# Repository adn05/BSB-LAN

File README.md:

# BSB-LPB-PPS-LAN

> **About this fork (branch content added on top of upstream BSB-LAN).**
> This repository adapts BSB-LAN to one **Atlantic Alféa Extensa Duo A.I.** heat pump (Siemens **RVS21**, family 211,
> variant 127, BSB bus on X86), running on an **ESP32-C3 SuperMini** plugged into a custom isolated interface board,
> and integrated into **Home Assistant** over MQTT. It is a personal project, not an official BSB-LAN release:
> for any other installation, use the [upstream project](https://github.com/fredlcore/BSB-LAN).
>
> Additions (the upstream code in `BSB_LAN/` only gets a few compile-time guards):
> - `alfea/config/`, `alfea/params/`: configuration, full 211/127 parameter list, Home Assistant selection, write whitelist;
> - `alfea/homeassistant/`: thermostat package (room setpoint overrides, DHW boost) and dashboard;
> - `alfea/hardware/`: interface board (KiCad 9) and 3D-printable enclosure;
> - `alfea/tools/`, `docker/`: build in Docker (`sh docker/compiler.sh`), flashing and USB console (`alfea/tools/flasher.py`);
> - documentation, in French: [`docs/claude/README.md`](docs/claude/README.md).

Die deutsche Fassung dieser Datei gibt es [hier](README_de.md).

Before getting started, please read through the manual [here](https://docs.bsb-lan.de).

BSB-LAN is a software/hardware solution for accessing the “Boiler-System-Bus” (BSB), the “Local-Process-Bus (LPB)” and the “Punkt-zu-Punkt-Schnittstelle” (PPS). The adapter is available for various *ESP32*-based microcontrollers (ESP32 NodeMCU, Olimex EVB, Olimex POE-ISO) as well as for an *Arduino Due* with Ethernet shield. It allows accessing the heating systems from Atlantic, Brötje, Elco and many other manufacturers via LAN/WLAN, provided that they use one of the Siemens controllers listed below. BSB-LAN makes it possible to control or regulate the heating and log any given values. This project supports almost all parameters available on the heating systems and can be used for in a comprehensive home automation environment.  

---

***Interface kits available!***  
**Interface boards are available for the ESP32 upon request. These can simply be plugged on top of one of the listed microcontrollers.Getting the board from here helps supporting this project in the future, so if you are interested, please send Frederik an e-mail (German or English) to <br /> bsb (ät) code-it.de <br /> for further informations.**  

---  

Using the adapter and the BSB-LAN software, various values and parameters can easily be monitored, logged and, if so desired, controlled and changed via a web-interface.
Optional integration into existing smart home systems such as FHEM, openHAB, HomeMatic, ioBroker, Loxone, IP-Symcon, EDOMI, Home Assistant, SmartHomeNG or Node-RED is possible via MQTT, JSON or HTTP access. 
The adapter can also be used as a standalone logger without LAN or Internet connection when using a microSD card (MBR partition / FAT format).  
Temperature and humidity sensors can also be connected and their data can also be logged and analyzed. The option of integrating your own code into the BSB-LAN software also offers a wide range of expansion options. 
        
**In the following, some model series from different manufacturers are listed, which usually have installed BSB-LAN compatible controllers:**  
- Brötje: BBK, BBS, BGB, BLW (**see exceptions below!**), BMK, BMR, BOB, BSK, BSW, Eurocontrol, ISR, LogoBloc, SGB, SOB, SPK, WBC (**see exceptions below!**), WBS (**see exceptions below!**), WGB (**see exceptions below!**), WMC, WMS, WOB
- **Not working Brötje models: BOK, BLW Eco, BLW Eco.2, BLW Mono, BLW Mono.1, BLW Neo, BLW Pro.1, BLW Split, BSW Neo, WBC 22.1/28.1, WBC 14.1/22.1, WGB-K 22.1/28.1, WGB 14.1/22.1/28.1/38.1, WHB, WHC, WHS, WLC, WLS and all others with IWR controller**  
- Bösch: heat pumps with RVS controller type
- Elco: Aerotop (**not EVO LN / Mono / Mono.2 / Split / Split.2!**), Aquatop, Rendamax, Straton, Thision (**not Thision Mini!**), Thision S, Thision S Plus, Trigon S Plus
- Alarko: Aldens WM/WS
- ATAG: QR
- Atlantic: Axeo, Alféa Excellia A.I., Alféa Extensa A.I., Hynea hybrid duo gaz, Navistem, Perfinox, Varmax
- Austria Email: LWP, LWPK
- Baxi: Luna Platinum, Luna Duo, Block Kondens
- Boesch: SLS
- Chappée: Luna, Klista
- CitrinSolar: proClima
- CTA: Optiheat
- CTC: 380 IC
- Deville: 9942, 9981
- District heating: RVD230
- Eco: AiWA, AW, BW, DW, heatLite, Star, TBW, WW, WWi, TWW
- Ecostar: Ecodense WT-S 45
- Etna: II GWS
- EVI Heat: Combi-7
- Ferroli: HMP
- Froeling: Rendagas Plus
- Fujitsu Waterstage: Comfort, Duo, WOHA, WSHA, WSYA, WSYK, WSYP
- Gebwell: T2
- Geminox: Thrs
- General: (aka Fujitsu Waterstage) WC13F / WOC13RIYF / WGHA 100DG
- Gorenje: Aerogor Compact, Aerogor Compact EVI, Aerogor ECO Inverter 10 A, Aerogor Split AW, Aerogor Split HD, Aerogor Split HD EVI, Aquagor, Aquagor EVI, Geogor All-In-One, Terragor, Terragor EVI
- Grünenwald: Greenheat
- GS: UnoTec
- Hansa: SND
- Herz: Commotherm 5 DeLuxe
- Hotjet: One2, Wx, ZETXe, ZETXi
- Ideal Heating: Halo Air, Logic Air Heat Pump
- Interdomo: Domostar GBK 25H/SH, OBK (HC 232)
- MAN/MHG: Ecostar 200
- MHG: ecoWP Xe, Procon E
- Oilon: CUBE House, GT, SH, SHx
- Olymp: RegelStar 3000, SHS, WHS
- Palazzetti: Choro Sistema Calore
- Potterton: Paramount
- Robur: Comfort Controller, K18 Simplygas / Hybrigas
- Sieger: TG11
- Šildymo Technologijų Centras (ŠTC): STC9
- Sixmadun: TG11BE
- Smartheat: UI400
- SSP: Proburner
- Strebel: S-ASX
- Sunex: Nexus
- Termomax: Termo ÖV
- Thercon: Therma Silent Coax Single, THERMA Silent Coax Combi 300/500
- Thermics: Energie
- Thermital: TBox Clima TOP
- Tifell: Biofell
- Variheat: 110C
- Viadrus : Claudius K1, K2
- Viessmann: Vitotwin 300-W (exclusively!)
- Wamak: AiWa, DB
- Weishaupt: WTU  

If your heater has one of the following controllers, but your model ist not listed in our manual, feel free to get in touch with us, as these models have been confirmed working:  
AVS37, AVS55, AVS71, AVS74, AVS75, AVS77, AVS79, LMS14, LMS15, LMS15, LMU64, LMU74, LMU75, RVA61, RVA63, RVA33, RVA36, RVA43, RVA46, RVA47, RVA53, RVA60, RVA61, RVA63, RVA65, RVA66, RVC32, RVD110, RVD115, RVD120, RVD125, RVD130, RVD135, RVD139, RVD140, RVD144, RVD145, RVD230, RVD235, RVD240, RVD245, RVD250, RVD255, RVD260, RVD265, RVL469, RVL470, RVL471, RVL472, RVL479, RVL480, RVL481, RVL482, RVP320, RVP330, RVP340, RVP350, RVP351, RVP360, RVP361, RVP5xx, RVS13, RVS21, RVS23, RVS26, RVS41, RVS43, RVS46, RVS47, RVS51, RVS53, RVS61, RVS63, RVS65, RVS68, RWI65, WRI80
<BR><BR>

<B>Attention!</B><BR>
Some companies which previously used BSB/LPB in their heating systems have now switched to other systems for their lower-cost devices. Examples are Brötje's WLC/WLS/BOK series. These are not compatible with BSB/LPB and only allow very limited parameters to be configured by the user. If you have one of these heating systems, you are so far out of luck to configure and monitor your heating system as it can be done with the more expensive (but BSB/LPB compatible) devices mentioned above among others.
In addition, there are now also Siemens controllers that no longer expose BSB/LPB connectors, but use different bus systems, for example the LMU34 and the Climatix/POS-series.
<BR><BR>
Instructions on how to configure etc. can be found in the <A HREF="https://docs.bsb-lan.de">manual</A>.<BR>
The forum thread that led to the development of this interface can be found <A HREF="http://forum.fhem.de/index.php?topic=29762.new;topicseen#new">here</A>.<BR>
(Forum is in German, but several members speak English)

Please take note that while the board can also be used on the Raspberry Pi, the software provided here only runs on the ESP32 and Arduino Due respectively! For using the board with the Pi, you have to use the software bsb_gateway which is available <A HREF="https://github.com/loehnertj/bsbgateway">here</A>. Please also note that the functionality differs significantly, and that you would have to contact the author of bsb_gateway for any question related to it.

Web-Interface screenshots:

BSB-Board populated for ESP32 Olimex boards:

BSB-Board on Olimex POE inside the project's 3D-printed case:

<br />This work is licensed under a <a rel="license" href="http://creativecommons.org/licenses/by-nc-sa/4.0/">Creative Commons Attribution-NonCommercial-ShareAlike 4.0 International License</a>.

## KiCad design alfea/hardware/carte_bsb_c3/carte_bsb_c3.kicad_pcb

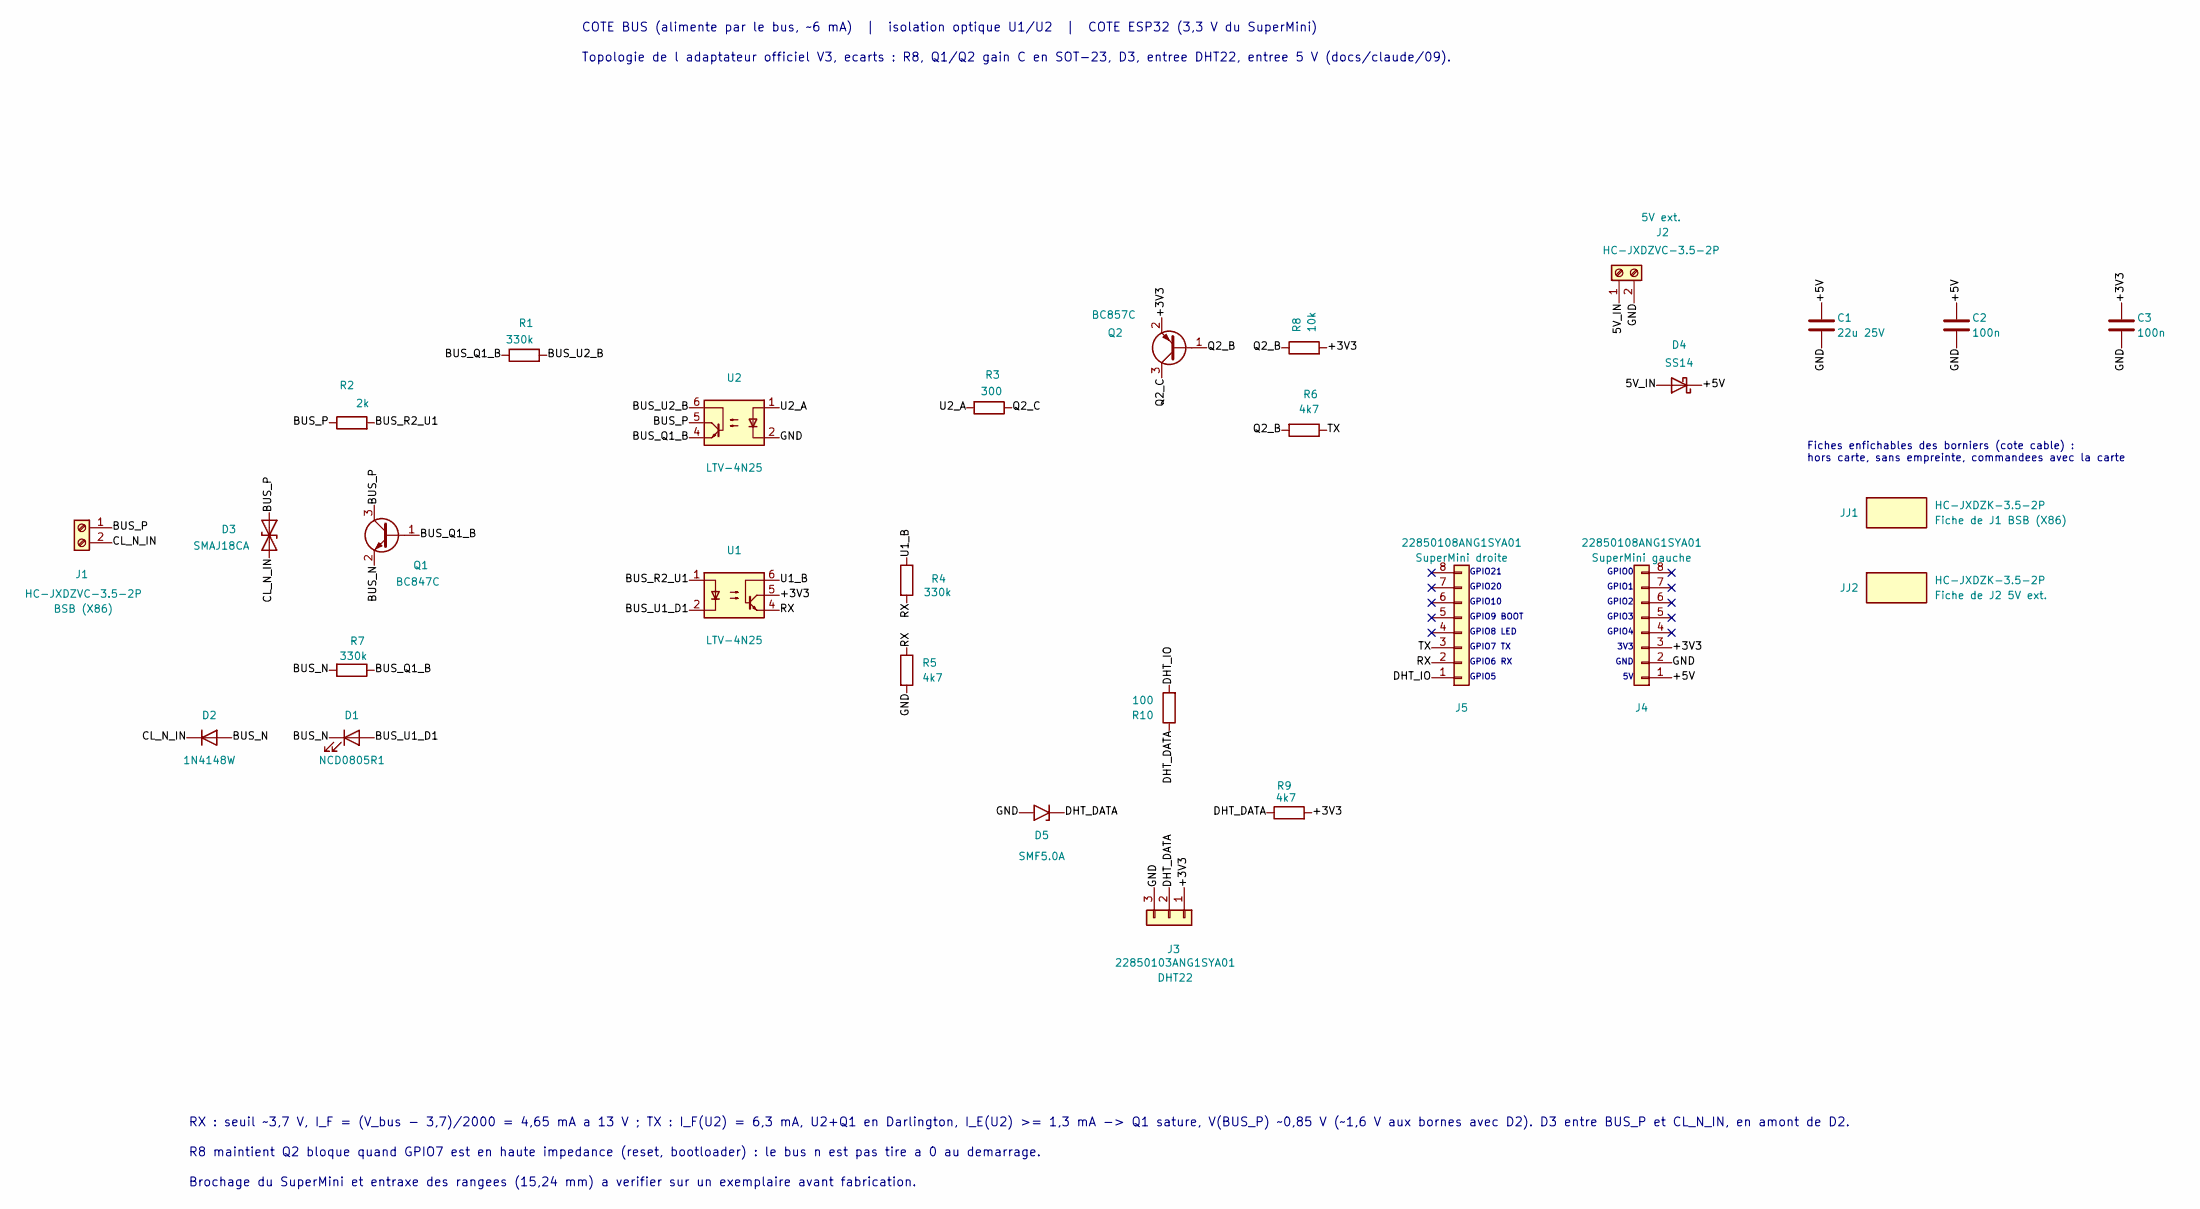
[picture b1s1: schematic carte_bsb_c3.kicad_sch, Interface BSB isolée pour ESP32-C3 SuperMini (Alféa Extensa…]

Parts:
C1: 22u 25V; C_1206_3216Metric; MPN Samsung Electro-Mechanics CL31A226KAHNN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; JLCPCB Part # C12891
C2, C3: 100n; C_0805_2012Metric; MPN YAGEO CC0805KRX7R9BB104; JLCPCB Part # C49678
D1: NCD0805R1; LED_0805_2012Metric; MPN Foshan NationStar Optoelectronics NCD08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; JLCPCB Part # C84256
D2: 1N4148W; D_SOD-123; MPN ST(Semtech) 1N4148W; JLCPCB Part # C81598
D3: SMAJ18CA; D_SMA; MPN hongjiacheng SMAJ18CA; JLCPCB Part # C19077539
D4: SS14; D_SMA; MPN MDD(Microdiode Semiconductor) SS14; JLCPCB Part # C2480
D5: SMF5.0A; D_SOD-123F; MPN hongjiacheng SMF5.0A; JLCPCB Part # C19077497
J1, J2: HC-JXDZVC-3.5-2P; PhoenixContact_MCV_1,5_2-G-3.5_1x02_P3.50mm_Vertical; MPN Hong Cheng HC-JXDZVC-3.5-2P; JLCPCB Part # C51927058
J3: 22850103ANG1SYA01; PinSocket_1x03_P2.54mm_Vertical; MPN JILN 22850103ANG1SYA01; JLCPCB Part # C41431926
J4, J5: 22850108ANG1SYA01; PinSocket_1x08_P2.54mm_Vertical; MPN JILN 22850108ANG1SYA01; JLCPCB Part # C429957
JJ1, JJ2: HC-JXDZK-3.5-2P; MPN Hong Cheng HC-JXDZK-3.5-2P; JLCPCB Part # C51927077
Q1: BC847C; SOT-23; MPN hongjiacheng BC847C; JLCPCB Part # C7420337
Q2: BC857C; SOT-23; MPN hongjiacheng BC857C; JLCPCB Part # C20069137
R1, R4, R7: 330k; R_0805_2012Metric; MPN UNI-ROYAL(Uniroyal Elec) 0805W8F3303T5E; JLCPCB Part # C17629
R2: 2k; R_1206_3216Metric; MPN UNI-ROYAL(Uniroyal Elec) 1206W4F2001T5E; JLCPCB Part # C17944
R3: 300; R_0805_2012Metric; MPN UNI-ROYAL(Uniroyal Elec) 0805W8F3000T5E; JLCPCB Part # C17617
R5, R6, R9: 4k7; R_0805_2012Metric; MPN UNI-ROYAL(Uniroyal Elec) 0805W8F4701T5E; JLCPCB Part # C17673
R8: 10k; R_0805_2012Metric; MPN UNI-ROYAL(Uniroyal Elec) 0805W8F1002T5E; JLCPCB Part # C17414
R10: 100; R_0805_2012Metric; MPN UNI-ROYAL(Uniroyal Elec) 0805W8F1000T5E; JLCPCB Part # C17408
U1, U2: LTV-4N25; DIP-6_W7.62mm; MPN Lite-On LTV-4N25; JLCPCB Part # C118160

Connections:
/5V_IN: D4.2 (A), J2.1
/+3V3: C3.1, J3.1, J4.3, Q2.2 (E), R8.2, R9.2, U1.5
/+5V: C1.1, C2.1, D4.1 (K), J4.1
/BUS_N: D1.1 (K), D2.2 (A), Q1.2 (E), R7.2
/BUS_P: D3.1 (A1), J1.1, Q1.3 (C), R2.1, U2.5
/BUS_Q1_B: Q1.1 (B), R1.1, R7.1, U2.4
/BUS_R2_U1: R2.2, U1.1
/BUS_U1_D1: D1.2 (A), U1.2
/BUS_U2_B: R1.2, U2.6
/CL_N_IN: D2.1 (K), D3.2 (A2), J1.2
/DHT_DATA: D5.1 (A1), J3.2, R9.1, R10.1
/DHT_IO: J5.1, R10.2
/GND: C1.2, C2.2, C3.2, D5.2 (A2), J2.2, J3.3, J4.2, R5.2, U2.2
/Q2_B: Q2.1 (B), R6.2, R8.1
/Q2_C: Q2.3 (C), R3.1
/RX: J5.2, R4.2, R5.1, U1.4
/TX: J5.3, R6.1
/U1_B: R4.1, U1.6
/U2_A: R3.2, U2.1

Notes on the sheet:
GPIO6 RX
RX : seuil ~3,7 V, I_F = (V_bus - 3,7)/2000 = 4,65 mA a 13 V ; TX : I_F(U2) = 6,3 mA, U2+Q1 en Darlington, I_E(U2) >= 1,3 mA -> Q1 sature, V(BUS_P) ~0,85 V (~1,6 V aux bornes avec D2). D3 entre BUS_P et CL_N_IN, en amont de D2.
GPIO1
Brochage du SuperMini et entraxe des rangees (15,24 mm) a verifier sur un exemplaire avant fabrication.
GPIO7 TX
GPIO3
GPIO20
GPIO9 BOOT
GPIO5
GPIO0
R8 maintient Q2 bloque quand GPIO7 est en haute impedance (reset, bootloader) : le bus n est pas tire a 0 au demarrage.
Topologie de l adaptateur officiel V3, ecarts : R8, Q1/Q2 gain C en SOT-23, D3, entree DHT22, entree 5 V (docs/claude/09).
3V3
GND
GPIO21
GPIO4
GPIO2
GPIO8 LED
GPIO10
COTE BUS (alimente par le bus, ~6 mA) | isolation optique U1/U2 | COTE ESP32 (3,3 V du SuperMini)
Fiches enfichables des borniers (cote cable) : hors carte, sans empreinte, commandees avec la carte

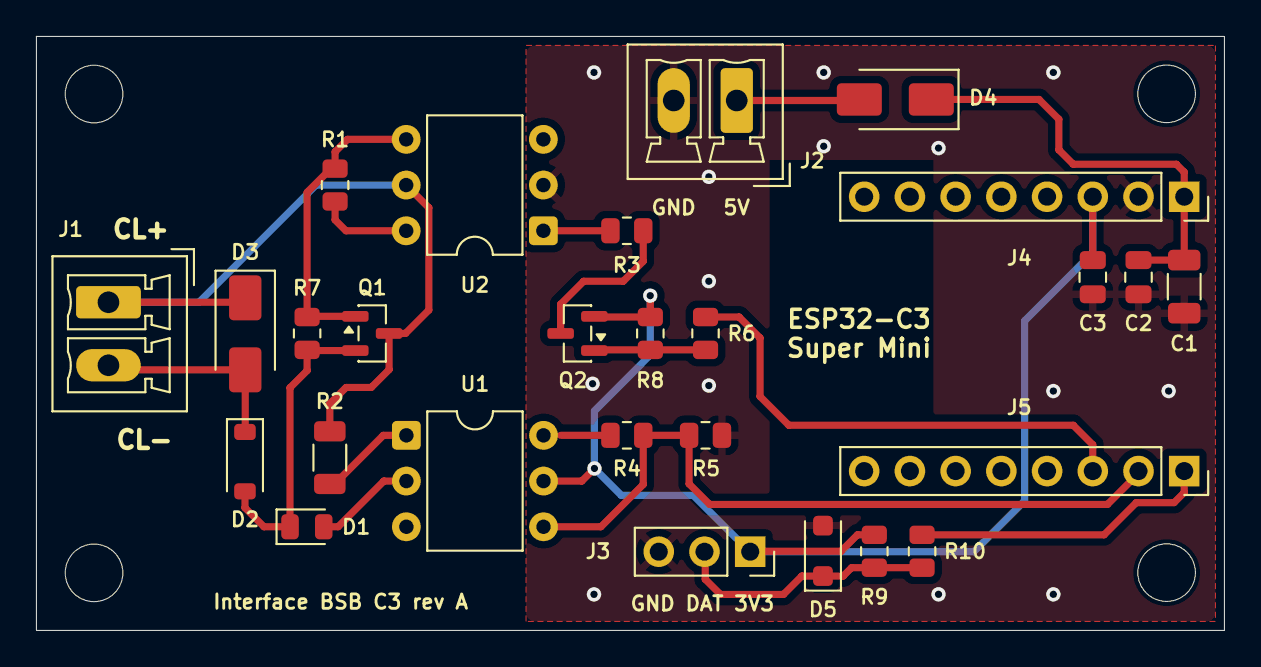
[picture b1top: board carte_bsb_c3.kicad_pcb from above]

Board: 2 copper layers, 66.0 x 33.0 mm, 31 parts (0 on the bottom side), 19 nets.

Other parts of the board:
H1, H2, H3, H4: MountingHole_3.2mm_M3

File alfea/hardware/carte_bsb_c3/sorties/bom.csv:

"Designator","Comment","Footprint","Quantity","JLCPCB Part #","Product link","MPN"
"C1","22u 25V","Capacitor_SMD:C_1206_3216Metric","1","C12891","https://jlcpcb.com/partdetail/13537-CL31A226KAHNNNE/C12891","Samsung Electro-Mechanics CL31A226KAHNNNE"
"C2,C3","100n","Capacitor_SMD:C_0805_2012Metric","2","C49678","https://jlcpcb.com/partdetail/YAGEO-CC0805KRX7R9BB104/C49678","YAGEO CC0805KRX7R9BB104"
"D1","NCD0805R1","LED_SMD:LED_0805_2012Metric","1","C84256","https://jlcpcb.com/partdetail/85425-NCD0805R1/C84256","Foshan NationStar Optoelectronics NCD0805R1"
"D2","1N4148W","Diode_SMD:D_SOD-123","1","C81598","https://jlcpcb.com/partdetail/ST_Semtech-1N4148W/C81598","ST(Semtech) 1N4148W"
"D3","SMAJ18CA","Diode_SMD:D_SMA","1","C19077539","https://jlcpcb.com/partdetail/hongjiacheng-SMAJ18CA/C19077539","hongjiacheng SMAJ18CA"
"D4","SS14","Diode_SMD:D_SMA","1","C2480","https://jlcpcb.com/partdetail/MDD_Microdiode_Semiconductor-S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","MDD(Microdiode Semiconductor) SS14"
"D5","SMF5.0A","Diode_SMD:D_SOD-123F","1","C19077497","https://jlcpcb.com/partdetail/hongjiacheng-SMF50A/C19077497","hongjiacheng SMF5.0A"
"J1,J2","HC-JXDZVC-3.5-2P","Connector_Phoenix_MC:PhoenixContact_MCV_1,5_2-G-3.5_1x02_P3.50mm_Vertical","2","C51927058","https://jlcpcb.com/partdetail/HongCheng-HC_JXDZVC_3_52P/C51927058","Hong Cheng HC-JXDZVC-3.5-2P"
"J3","22850103ANG1SYA01","Connector_PinSocket_2.54mm:PinSocket_1x03_P2.54mm_Vertical","1","C41431926","https://jlcpcb.com/partdetail/JILN-22850103ANG1SYA01/C41431926","JILN 22850103ANG1SYA01"
"J4,J5","22850108ANG1SYA01","Connector_PinSocket_2.54mm:PinSocket_1x08_P2.54mm_Vertical","2","C429957","https://jlcpcb.com/partdetail/JILN-22850108ANG1SYA01/C429957","JILN 22850108ANG1SYA01"
"JJ1,JJ2","HC-JXDZK-3.5-2P","","2","C51927077","https://jlcpcb.com/partdetail/HongCheng-HC_JXDZK_3_52P/C51927077","Hong Cheng HC-JXDZK-3.5-2P"
"Q1","BC847C","Package_TO_SOT_SMD:SOT-23","1","C7420337","https://jlcpcb.com/partdetail/hongjiacheng-BC847C/C7420337","hongjiacheng BC847C"
"Q2","BC857C","Package_TO_SOT_SMD:SOT-23","1","C20069137","https://jlcpcb.com/partdetail/hongjiacheng-BC857C/C20069137","hongjiacheng BC857C"
"R1,R4,R7","330k","Resistor_SMD:R_0805_2012Metric","3","C17629","https://jlcpcb.com/partdetail/18317-0805W8F3303T5E/C17629","UNI-ROYAL(Uniroyal Elec) 0805W8F3303T5E"
"R2","2k","Resistor_SMD:R_1206_3216Metric","1","C17944","https://jlcpcb.com/partdetail/18632-1206W4F2001T5E/C17944","UNI-ROYAL(Uniroyal Elec) 1206W4F2001T5E"
"R3","300","Resistor_SMD:R_0805_2012Metric","1","C17617","https://jlcpcb.com/partdetail/18305-0805W8F3000T5E/C17617","UNI-ROYAL(Uniroyal Elec) 0805W8F3000T5E"
"R5,R6,R9","4k7","Resistor_SMD:R_0805_2012Metric","3","C17673","https://jlcpcb.com/partdetail/18361-0805W8F4701T5E/C17673","UNI-ROYAL(Uniroyal Elec) 0805W8F4701T5E"
"R8","10k","Resistor_SMD:R_0805_2012Metric","1","C17414","https://jlcpcb.com/partdetail/18102-0805W8F1002T5E/C17414","UNI-ROYAL(Uniroyal Elec) 0805W8F1002T5E"
"R10","100","Resistor_SMD:R_0805_2012Metric","1","C17408","https://jlcpcb.com/partdetail/18096-0805W8F1000T5E/C17408","UNI-ROYAL(Uniroyal Elec) 0805W8F1000T5E"
"U1,U2","LTV-4N25","Package_DIP:DIP-6_W7.62mm","2","C118160","https://jlcpcb.com/partdetail/LiteOn-LTV4N25/C118160","Lite-On LTV-4N25"

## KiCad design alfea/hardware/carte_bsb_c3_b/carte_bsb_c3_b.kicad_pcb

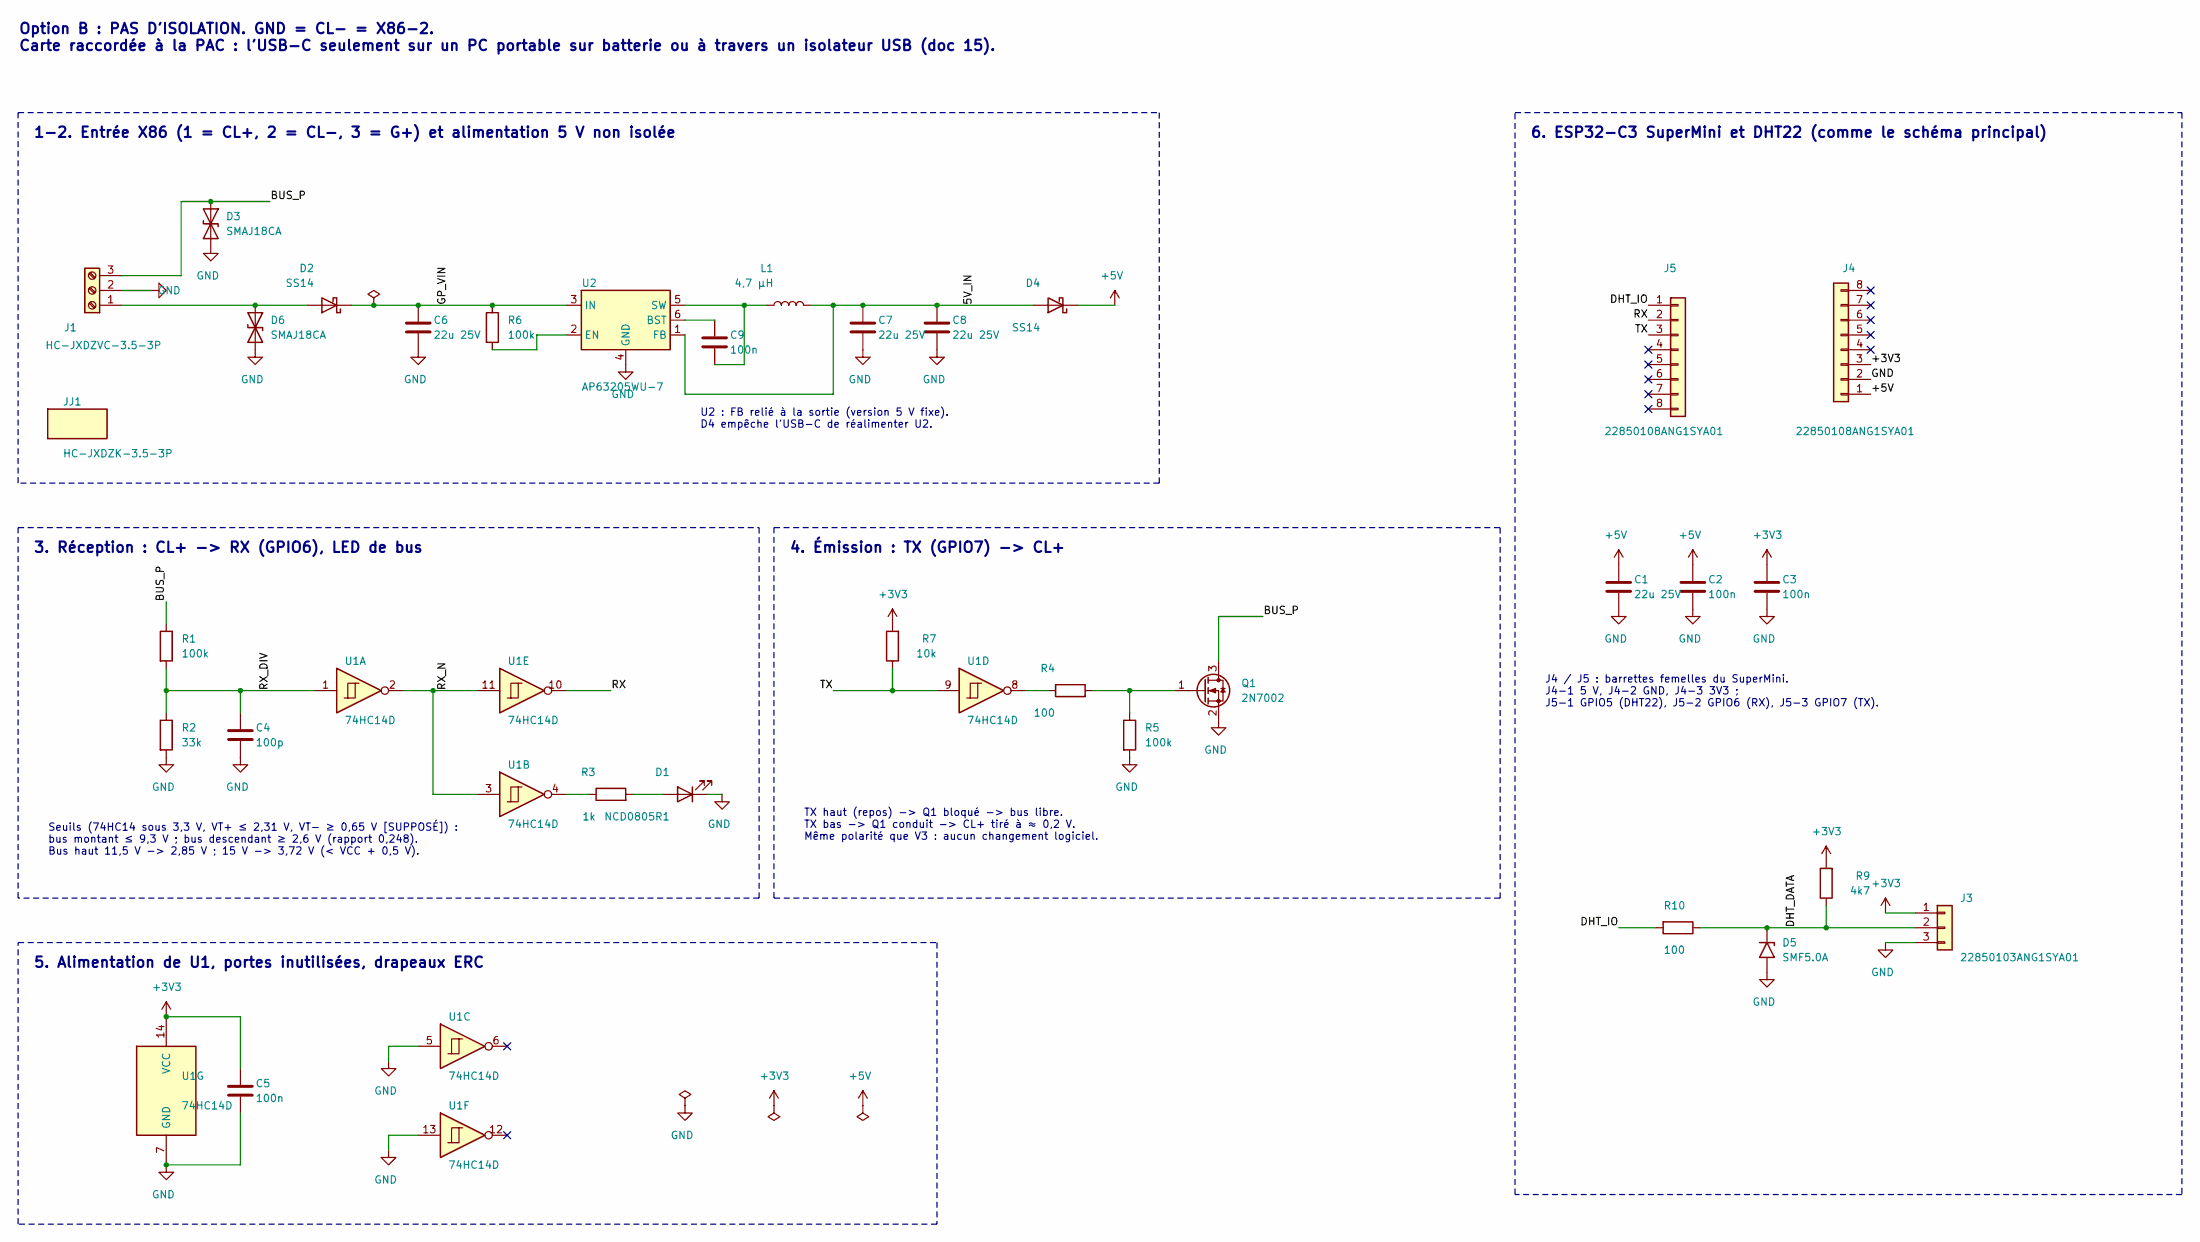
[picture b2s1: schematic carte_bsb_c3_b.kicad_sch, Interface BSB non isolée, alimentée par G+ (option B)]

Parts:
C1, C6, C7, C8: 22u 25V; C_1206_3216Metric; MPN Samsung Electro-Mechanics CL31A226KAHNN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; JLCPCB Part # C12891
C2, C3, C5, C9: 100n; C_0805_2012Metric; MPN YAGEO CC0805KRX7R9BB104; JLCPCB Part # C49678
C4: 100p; C_0805_2012Metric; MPN Samsung Electro-Mechanics CL21C101JBANN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; JLCPCB Part # C1790
D1: NCD0805R1; LED_0805_2012Metric; MPN Foshan NationStar Optoelectronics NCD08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; JLCPCB Part # C84256
D2, D4: SS14; D_SMA; MPN MDD(Microdiode Semiconductor) SS14; JLCPCB Part # C2480
D3, D6: SMAJ18CA; D_SMA; MPN hongjiacheng SMAJ18CA; JLCPCB Part # C19077539
D5: SMF5.0A; D_SOD-123F; MPN hongjiacheng SMF5.0A; JLCPCB Part # C19077497
J1: HC-JXDZVC-3.5-3P; PhoenixContact_MCV_1,5_3-G-3.5_1x03_P3.50mm_Vertical; MPN Hong Cheng HC-JXDZVC-3.5-3P; JLCPCB Part # C51927059
J3: 22850103ANG1SYA01; PinSocket_1x03_P2.54mm_Vertical; MPN JILN 22850103ANG1SYA01; JLCPCB Part # C41431926
J4, J5: 22850108ANG1SYA01; PinSocket_1x08_P2.54mm_Vertical; MPN JILN 22850108ANG1SYA01; JLCPCB Part # C429957
JJ1: HC-JXDZK-3.5-3P; MPN Hong Cheng HC-JXDZK-3.5-3P; JLCPCB Part # C51927078
L1: 4,7 µH; L_Sunlord_SWPA4030S; MPN Sunlord SWPA4030S4R7MT; JLCPCB Part # C57269
Q1: 2N7002; SOT-23; MPN Jiangsu Changjing 2N7002; JLCPCB Part # C8545
R1, R5, R6: 100k; R_0805_2012Metric; MPN UNI-ROYAL(Uniroyal Elec) 0805W8F1003T5E; JLCPCB Part # C149504
R2: 33k; R_0805_2012Metric; MPN UNI-ROYAL(Uniroyal Elec) 0805W8F3302T5E; JLCPCB Part # C17633
R3: 1k; R_0805_2012Metric; MPN UNI-ROYAL(Uniroyal Elec) 0805W8F1001T5E; JLCPCB Part # C17513
R4, R10: 100; R_0805_2012Metric; MPN UNI-ROYAL(Uniroyal Elec) 0805W8F1000T5E; JLCPCB Part # C17408
R7: 10k; R_0805_2012Metric; MPN UNI-ROYAL(Uniroyal Elec) 0805W8F1002T5E; JLCPCB Part # C17414
R9: 4k7; R_0805_2012Metric; MPN UNI-ROYAL(Uniroyal Elec) 0805W8F4701T5E; JLCPCB Part # C17673
U1: 74HC14D; SOIC-14_3.9x8.7mm_P1.27mm; MPN Nexperia 74HC14D,653; JLCPCB Part # C5605
U2: AP63205WU-7; TSOT-23-6; MPN Diodes Incorporated AP63205WU-7; JLCPCB Part # C2071056

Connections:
+3V3: C3.1, C5.1, J3.1, J4.3, R7.2, R9.2, U1.14 (VCC)
+5V: C1.1, C2.1, D4.1 (K), J4.1
/5V_IN: C7.1, C8.1, D4.2 (A), L1.2, U2.1 (FB)
/BUS_P: D3.1 (A1), J1.3, Q1.3 (D), R1.1
/DHT_DATA: D5.1 (A1), J3.2, R9.1, R10.1
/DHT_IO: J5.1, R10.2
/GP_VIN: C6.1, D2.1 (K), R6.1, U2.3 (IN)
/RX: J5.2, U1.10
/RX_DIV: C4.1, R1.2, R2.1, U1.1
/RX_N: U1.2, U1.3, U1.11
/TX: J5.3, R7.1, U1.9
GND: C1.2, C2.2, C3.2, C4.2, C5.2, C6.2, C7.2, C8.2, D1.1 (K), D3.2 (A2), D5.2 (A2), D6.2 (A2), J1.2, J3.3, J4.2, Q1.2 (S), R2.2, R5.2, U1.5, U1.7 (GND), U1.13, U2.4 (GND)
unnamed: D1.2 (A), R3.2
unnamed: D2.2 (A), D6.1 (A1), J1.1
unnamed: Q1.1 (G), R4.2, R5.1
unnamed: R3.1, U1.4
unnamed: R4.1, U1.8
unnamed: C9.1, U2.6 (BST)
unnamed: R6.2, U2.2 (EN)
unnamed: C9.2, L1.1, U2.5 (SW)

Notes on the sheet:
Seuils (74HC14 sous 3,3 V, VT+ ≤ 2,31 V, VT- ≥ 0,65 V [SUPPOSÉ]) : bus montant ≤ 9,3 V ; bus descendant ≥ 2,6 V (rapport 0,248). Bus haut 11,5 V -> 2,85 V ; 15 V -> 3,72 V (< VCC + 0,5 V).
5. Alimentation de U1, portes inutilisées, drapeaux ERC
U2 : FB relié à la sortie (version 5 V fixe). D4 empêche l'USB-C de réalimenter U2.
Option B : PAS D'ISOLATION. GND = CL- = X86-2. Carte raccordée à la PAC : l'USB-C seulement sur un PC portable sur batterie ou à travers un isolateur USB (doc 15).
1-2. Entrée X86 (1 = CL+, 2 = CL-, 3 = G+) et alimentation 5 V non isolée
4. Émission : TX (GPIO7) -> CL+
6. ESP32-C3 SuperMini et DHT22 (comme le schéma principal)
3. Réception : CL+ -> RX (GPIO6), LED de bus
J4 / J5 : barrettes femelles du SuperMini. J4-1 5 V, J4-2 GND, J4-3 3V3 ; J5-1 GPIO5 (DHT22), J5-2 GPIO6 (RX), J5-3 GPIO7 (TX).
TX haut (repos) -> Q1 bloqué -> bus libre. TX bas -> Q1 conduit -> CL+ tiré à ≈ 0,2 V. Même polarité que V3 : aucun changement logiciel.

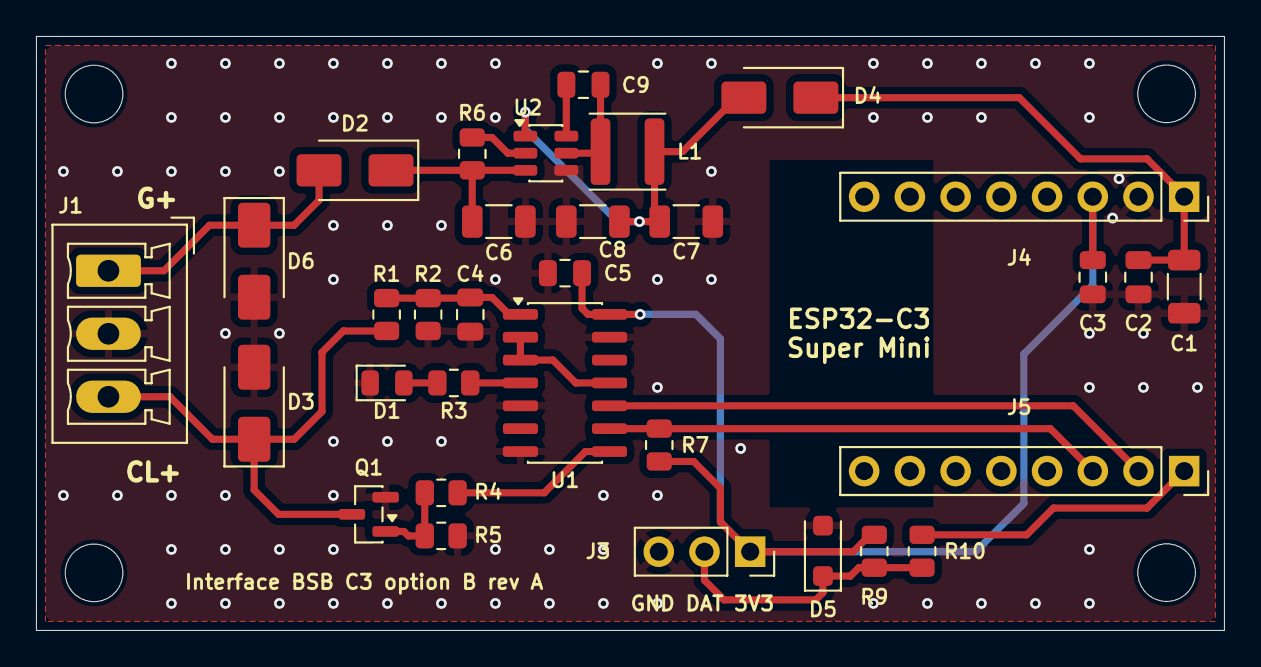
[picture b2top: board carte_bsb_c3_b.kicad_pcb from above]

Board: 2 copper layers, 66.0 x 33.0 mm, 36 parts (0 on the bottom side), 20 nets.

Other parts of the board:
H1, H2, H3, H4: MountingHole_3.2mm_M3

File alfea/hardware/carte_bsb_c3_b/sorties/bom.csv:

"Designator","Comment","Footprint","Quantity","JLCPCB Part #","MPN"
"C1,C6,C7,C8","22u 25V","Capacitor_SMD:C_1206_3216Metric","4","C12891","Samsung Electro-Mechanics CL31A226KAHNNNE"
"C2,C3,C5,C9","100n","Capacitor_SMD:C_0805_2012Metric","4","C49678","YAGEO CC0805KRX7R9BB104"
"C4","100p","Capacitor_SMD:C_0805_2012Metric","1","C1790","Samsung Electro-Mechanics CL21C101JBANNNC"
"D1","NCD0805R1","LED_SMD:LED_0805_2012Metric","1","C84256","Foshan NationStar Optoelectronics NCD0805R1"
"D2,D4","SS14","Diode_SMD:D_SMA","2","C2480","MDD(Microdiode Semiconductor) SS14"
"D3,D6","SMAJ18CA","Diode_SMD:D_SMA","2","C19077539","hongjiacheng SMAJ18CA"
"D5","SMF5.0A","Diode_SMD:D_SOD-123F","1","C19077497","hongjiacheng SMF5.0A"
"J1","HC-JXDZVC-3.5-3P","Connector_Phoenix_MC:PhoenixContact_MCV_1,5_3-G-3.5_1x03_P3.50mm_Vertical","1","C51927059","Hong Cheng HC-JXDZVC-3.5-3P"
"J3","22850103ANG1SYA01","Connector_PinSocket_2.54mm:PinSocket_1x03_P2.54mm_Vertical","1","C41431926","JILN 22850103ANG1SYA01"
"J4,J5","22850108ANG1SYA01","Connector_PinSocket_2.54mm:PinSocket_1x08_P2.54mm_Vertical","2","C429957","JILN 22850108ANG1SYA01"
"JJ1","HC-JXDZK-3.5-3P","","1","C51927078","Hong Cheng HC-JXDZK-3.5-3P"
"L1","4,7 µH","Inductor_SMD:L_Sunlord_SWPA4030S","1","C57269","Sunlord SWPA4030S4R7MT"
"Q1","2N7002","Package_TO_SOT_SMD:SOT-23","1","C8545","Jiangsu Changjing 2N7002"
"R1,R5,R6","100k","Resistor_SMD:R_0805_2012Metric","3","C149504","UNI-ROYAL(Uniroyal Elec) 0805W8F1003T5E"
"R2","33k","Resistor_SMD:R_0805_2012Metric","1","C17633","UNI-ROYAL(Uniroyal Elec) 0805W8F3302T5E"
"R3","1k","Resistor_SMD:R_0805_2012Metric","1","C17513","UNI-ROYAL(Uniroyal Elec) 0805W8F1001T5E"
"R4,R10","100","Resistor_SMD:R_0805_2012Metric","2","C17408","UNI-ROYAL(Uniroyal Elec) 0805W8F1000T5E"
"R7","10k","Resistor_SMD:R_0805_2012Metric","1","C17414","UNI-ROYAL(Uniroyal Elec) 0805W8F1002T5E"
"R9","4k7","Resistor_SMD:R_0805_2012Metric","1","C17673","UNI-ROYAL(Uniroyal Elec) 0805W8F4701T5E"
"U1","74HC14D","Package_SO:SOIC-14_3.9x8.7mm_P1.27mm","1","C5605","Nexperia 74HC14D,653"
"U2","AP63205WU-7","Package_TO_SOT_SMD:TSOT-23-6","1","C2071056","Diodes Incorporated AP63205WU-7"

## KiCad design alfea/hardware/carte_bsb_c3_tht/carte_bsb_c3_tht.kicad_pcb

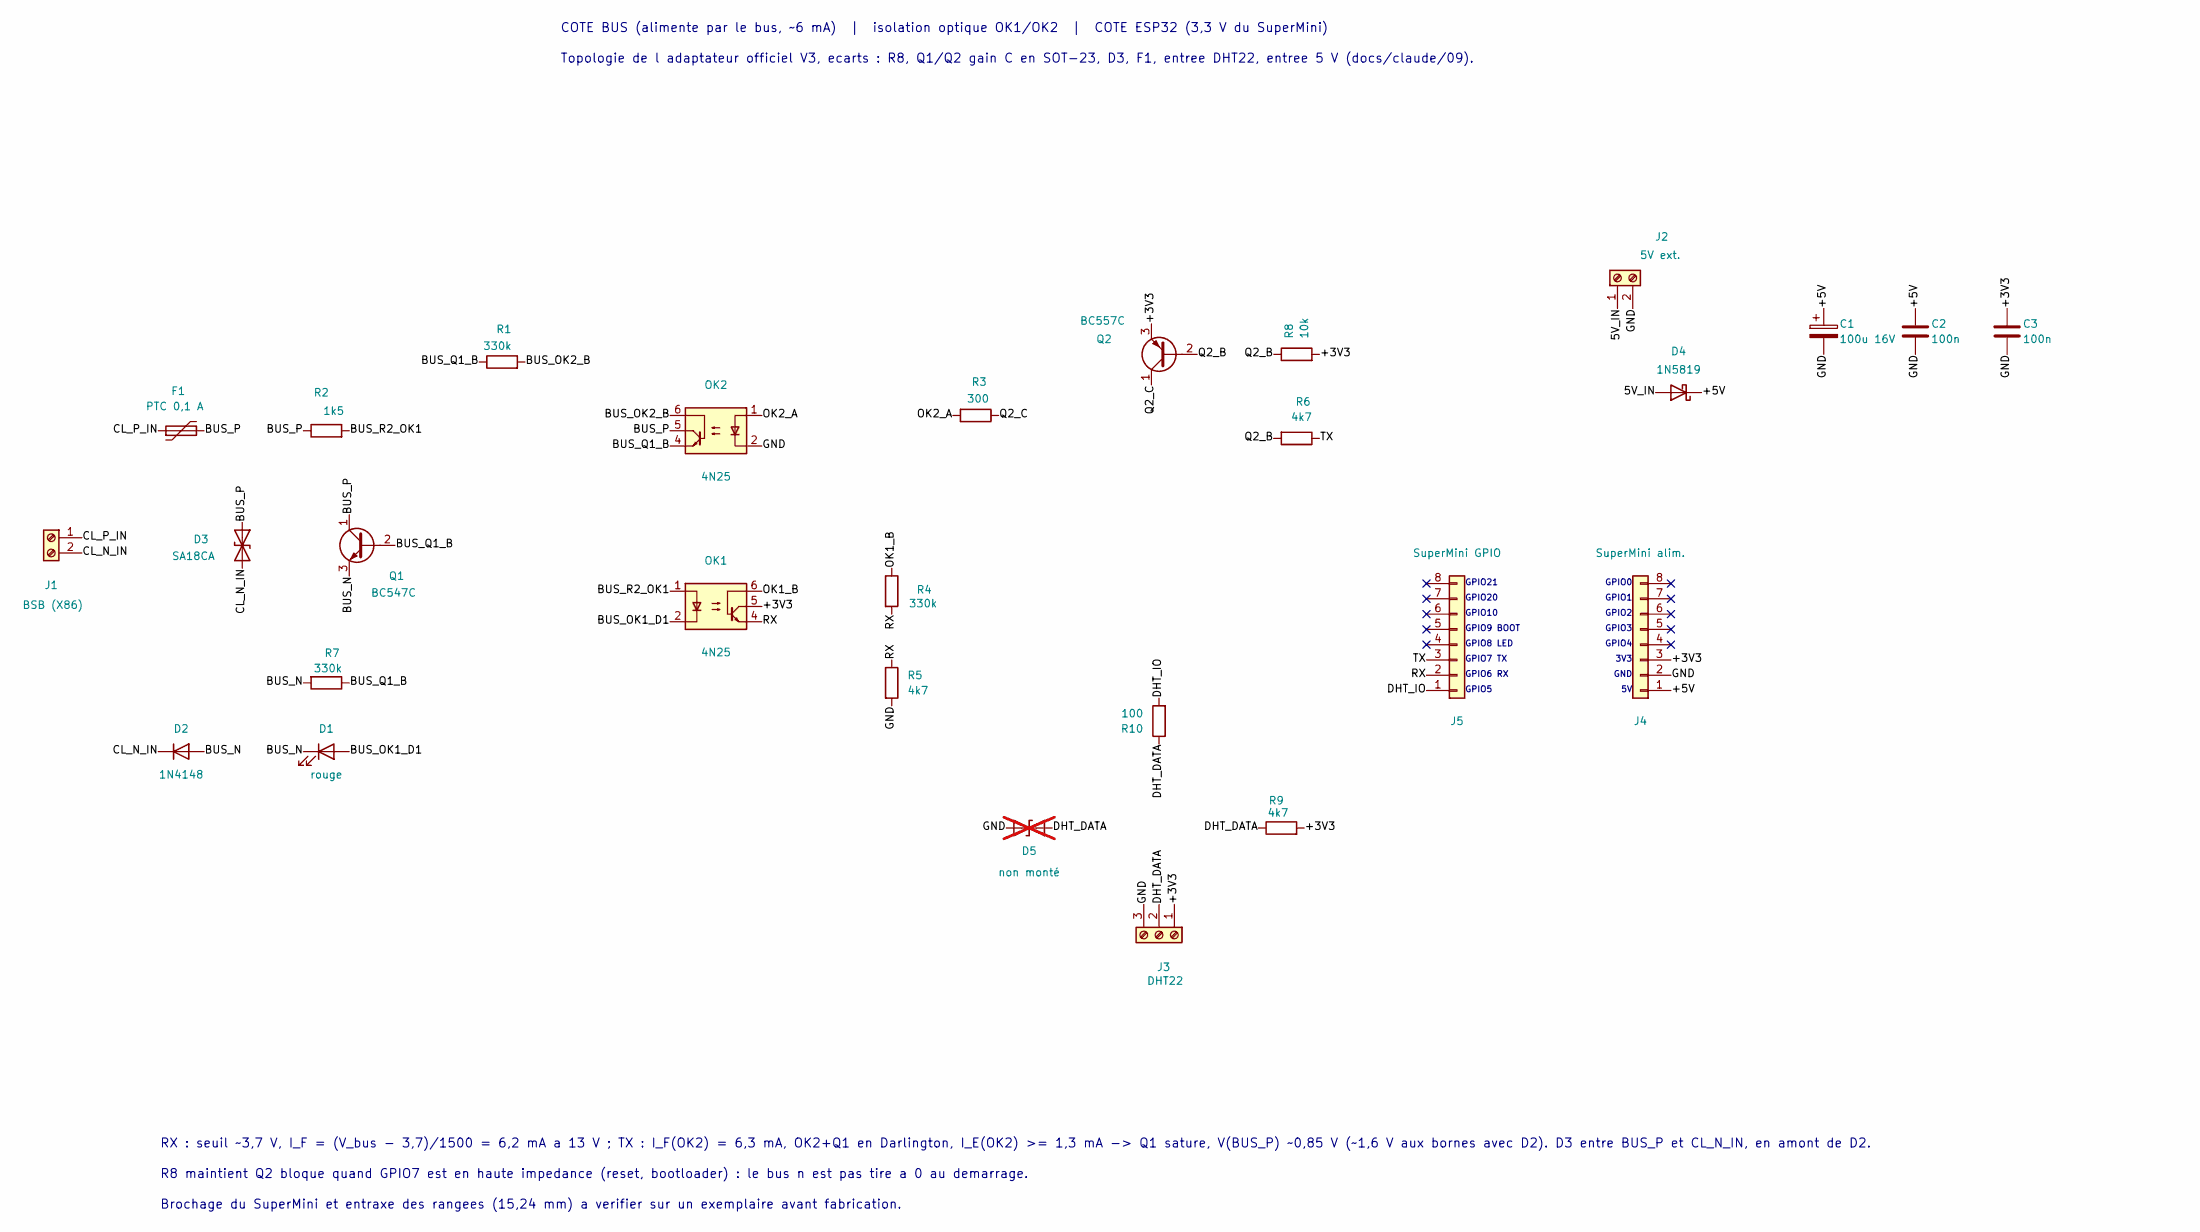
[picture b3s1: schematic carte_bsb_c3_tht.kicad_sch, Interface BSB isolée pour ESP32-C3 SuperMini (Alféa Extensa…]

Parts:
C1: 100u 16V; CP_Radial_D5.0mm_P2.50mm; MPN 100 uF 16 V radial D5
C2, C3: 100n; C_Disc_D3.0mm_W2.0mm_P2.50mm; MPN 100 nF X7R 50 V
D1: rouge; LED_D3.0mm; MPN LED rouge 3 mm
D2: 1N4148; D_DO-35_SOD27_P7.62mm_Horizontal; MPN 1N4148 (DO-35)
D3: SA18CA; D_DO-15_P2.54mm_Vertical_AnodeUp; MPN Littelfuse SA18CA (500 W, DO-15)
D4: 1N5819; D_DO-41_SOD81_P5.08mm_Vertical_AnodeUp; MPN 1N5819 (Schottky 1 A, 40 V)
D5: non monté; D_DO-35_SOD27_P2.54mm_Vertical_AnodeUp; MPN emplacement libre (option ESD, voir 09b); not fitted
F1: PTC 0,1 A; PTC_Radial_P5.08mm; MPN Bourns MF-R010 (radiale, pas 5,1 mm)
J1: BSB (X86); TerminalBlock_Phoenix_MPT-0,5-2-2.54_1x02_P2.54mm_Horizontal; MPN Phoenix MPT 0,5/2-2,54
J2: 5V ext.; TerminalBlock_Phoenix_MPT-0,5-2-2.54_1x02_P2.54mm_Horizontal; MPN Phoenix MPT 0,5/2-2,54
J3: DHT22; TerminalBlock_Phoenix_MPT-0,5-3-2.54_1x03_P2.54mm_Horizontal; MPN Phoenix MPT 0,5/3-2,54
J4: SuperMini alim.; PinSocket_1x08_P2.54mm_Vertical; MPN barrette femelle 1x8 2,54 mm
J5: SuperMini GPIO; PinSocket_1x08_P2.54mm_Vertical; MPN barrette femelle 1x8 2,54 mm
OK1, OK2: 4N25; DIP-6_W7.62mm; MPN Vishay 4N25
Q1: BC547C; TO-92_Inline_Wide; MPN BC547C
Q2: BC557C; TO-92_Inline_Wide; MPN BC557C
R1, R4: 330k; R_Axial_DIN0207_L6.3mm_D2.5mm_P5.08mm_Vertical; MPN 330 kOhm 1 % 0,25 W
R2: 1k5; R_Axial_DIN0207_L6.3mm_D2.5mm_P7.62mm_Horizontal; MPN 1,5 kOhm 1 % 0,25 W
R3: 300; R_Axial_DIN0207_L6.3mm_D2.5mm_P2.54mm_Vertical; MPN 300 Ohm 1 % 0,25 W
R5: 4k7; R_Axial_DIN0207_L6.3mm_D2.5mm_P10.16mm_Horizontal; MPN 4,7 kOhm 1 % 0,25 W
R6, R9: 4k7; R_Axial_DIN0207_L6.3mm_D2.5mm_P2.54mm_Vertical; MPN 4,7 kOhm 1 % 0,25 W
R7: 330k; R_Axial_DIN0207_L6.3mm_D2.5mm_P2.54mm_Vertical; MPN 330 kOhm 1 % 0,25 W
R8: 10k; R_Axial_DIN0207_L6.3mm_D2.5mm_P2.54mm_Vertical; MPN 10 kOhm 1 % 0,25 W
R10: 100; R_Axial_DIN0207_L6.3mm_D2.5mm_P5.08mm_Vertical; MPN 100 Ohm 0,25 W

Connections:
/5V_IN: D4.2 (A), J2.1
/+3V3: C3.1, J3.1, J4.3, OK1.5, Q2.3 (E), R8.2, R9.2
/+5V: C1.1, C2.1, D4.1 (K), J4.1
/BUS_N: D1.1 (K), D2.2 (A), Q1.3 (E), R7.2
/BUS_OK1_D1: D1.2 (A), OK1.2
/BUS_OK2_B: OK2.6, R1.2
/BUS_P: D3.1 (A1), F1.2, OK2.5, Q1.1 (C), R2.1
/BUS_Q1_B: OK2.4, Q1.2 (B), R1.1, R7.1
/BUS_R2_OK1: OK1.1, R2.2
/CL_N_IN: D2.1 (K), D3.2 (A2), J1.2
/CL_P_IN: F1.1, J1.1
/DHT_DATA: D5.1 (A1), J3.2, R9.1, R10.1
/DHT_IO: J5.1, R10.2
/GND: C1.2, C2.2, C3.2, D5.2 (A2), J2.2, J3.3, J4.2, OK2.2, R5.2
/OK1_B: OK1.6, R4.1
/OK2_A: OK2.1, R3.2
/Q2_B: Q2.2 (B), R6.2, R8.1
/Q2_C: Q2.1 (C), R3.1
/RX: J5.2, OK1.4, R4.2, R5.1
/TX: J5.3, R6.1

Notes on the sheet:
GPIO6 RX
RX : seuil ~3,7 V, I_F = (V_bus - 3,7)/1500 = 6,2 mA a 13 V ; TX : I_F(OK2) = 6,3 mA, OK2+Q1 en Darlington, I_E(OK2) >= 1,3 mA -> Q1 sature, V(BUS_P) ~0,85 V (~1,6 V aux bornes avec D2). D3 entre BUS_P et CL_N_IN, en amont de D2.
GPIO1
Brochage du SuperMini et entraxe des rangees (15,24 mm) a verifier sur un exemplaire avant fabrication.
GPIO7 TX
GPIO3
GPIO20
GPIO9 BOOT
GPIO5
GPIO0
R8 maintient Q2 bloque quand GPIO7 est en haute impedance (reset, bootloader) : le bus n est pas tire a 0 au demarrage.
Topologie de l adaptateur officiel V3, ecarts : R8, Q1/Q2 gain C en SOT-23, D3, F1, entree DHT22, entree 5 V (docs/claude/09).
3V3
GND
GPIO21
GPIO4
GPIO2
GPIO8 LED
GPIO10
COTE BUS (alimente par le bus, ~6 mA) | isolation optique OK1/OK2 | COTE ESP32 (3,3 V du SuperMini)

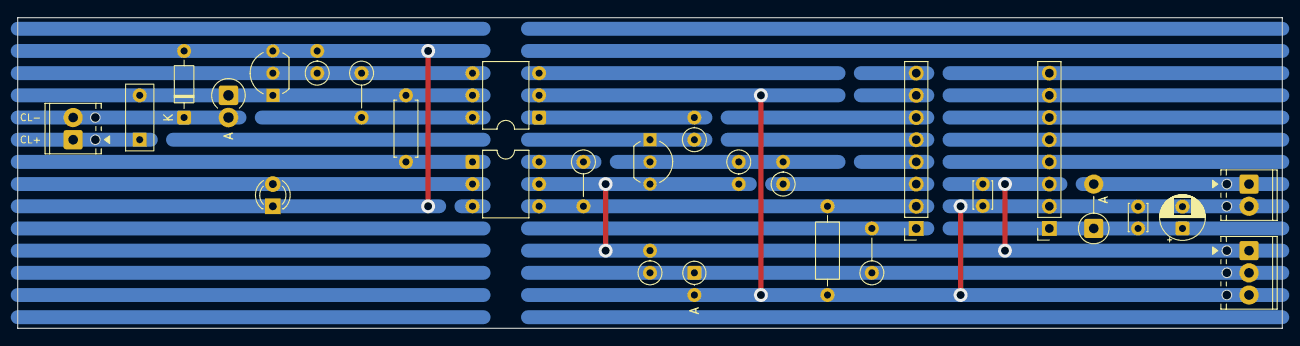
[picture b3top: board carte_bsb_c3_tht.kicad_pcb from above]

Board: 2 copper layers, 144.8 x 35.6 mm, 28 parts (0 on the bottom side), 20 nets.

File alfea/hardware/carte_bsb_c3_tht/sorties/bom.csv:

"Reference","Value","Footprint","MPN","QUANTITY"
"C1","100u 16V","Capacitor_THT:CP_Radial_D5.0mm_P2.50mm","100 uF 16 V radial D5","1"
"C2,C3","100n","Capacitor_THT:C_Disc_D3.0mm_W2.0mm_P2.50mm","100 nF X7R 50 V","2"
"D1","rouge","LED_THT:LED_D3.0mm","LED rouge 3 mm","1"
"D2","1N4148","Diode_THT:D_DO-35_SOD27_P7.62mm_Horizontal","1N4148 (DO-35)","1"
"D3","SA18CA","Diode_THT:D_DO-15_P2.54mm_Vertical_AnodeUp","Littelfuse SA18CA (500 W, DO-15)","1"
"D4","1N5819","Diode_THT:D_DO-41_SOD81_P5.08mm_Vertical_AnodeUp","1N5819 (Schottky 1 A, 40 V)","1"
"F1","PTC 0,1 A","alfea_tht:PTC_Radial_P5.08mm","Bourns MF-R010 (radiale, pas 5,1 mm)","1"
"J1","BSB (X86)","TerminalBlock_Phoenix:TerminalBlock_Phoenix_MPT-0,5-2-2.54_1x02_P2.54mm_Horizontal","Phoenix MPT 0,5/2-2,54","1"
"J2","5V ext.","TerminalBlock_Phoenix:TerminalBlock_Phoenix_MPT-0,5-2-2.54_1x02_P2.54mm_Horizontal","Phoenix MPT 0,5/2-2,54","1"
"J3","DHT22","TerminalBlock_Phoenix:TerminalBlock_Phoenix_MPT-0,5-3-2.54_1x03_P2.54mm_Horizontal","Phoenix MPT 0,5/3-2,54","1"
"J4","SuperMini alim.","Connector_PinSocket_2.54mm:PinSocket_1x08_P2.54mm_Vertical","barrette femelle 1x8 2,54 mm","1"
"J5","SuperMini GPIO","Connector_PinSocket_2.54mm:PinSocket_1x08_P2.54mm_Vertical","barrette femelle 1x8 2,54 mm","1"
"OK1,OK2","4N25","Package_DIP:DIP-6_W7.62mm","Vishay 4N25","2"
"Q1","BC547C","Package_TO_SOT_THT:TO-92_Inline_Wide","BC547C","1"
"Q2","BC557C","Package_TO_SOT_THT:TO-92_Inline_Wide","BC557C","1"
"R1,R4","330k","Resistor_THT:R_Axial_DIN0207_L6.3mm_D2.5mm_P5.08mm_Vertical","330 kOhm 1 % 0,25 W","2"
"R2","1k5","Resistor_THT:R_Axial_DIN0207_L6.3mm_D2.5mm_P7.62mm_Horizontal","1,5 kOhm 1 % 0,25 W","1"
"R3","300","Resistor_THT:R_Axial_DIN0207_L6.3mm_D2.5mm_P2.54mm_Vertical","300 Ohm 1 % 0,25 W","1"
"R5","4k7","Resistor_THT:R_Axial_DIN0207_L6.3mm_D2.5mm_P10.16mm_Horizontal","4,7 kOhm 1 % 0,25 W","1"
"R6,R9","4k7","Resistor_THT:R_Axial_DIN0207_L6.3mm_D2.5mm_P2.54mm_Vertical","4,7 kOhm 1 % 0,25 W","2"
"R7","330k","Resistor_THT:R_Axial_DIN0207_L6.3mm_D2.5mm_P2.54mm_Vertical","330 kOhm 1 % 0,25 W","1"
"R8","10k","Resistor_THT:R_Axial_DIN0207_L6.3mm_D2.5mm_P2.54mm_Vertical","10 kOhm 1 % 0,25 W","1"
"R10","100","Resistor_THT:R_Axial_DIN0207_L6.3mm_D2.5mm_P5.08mm_Vertical","100 Ohm 0,25 W","1"
